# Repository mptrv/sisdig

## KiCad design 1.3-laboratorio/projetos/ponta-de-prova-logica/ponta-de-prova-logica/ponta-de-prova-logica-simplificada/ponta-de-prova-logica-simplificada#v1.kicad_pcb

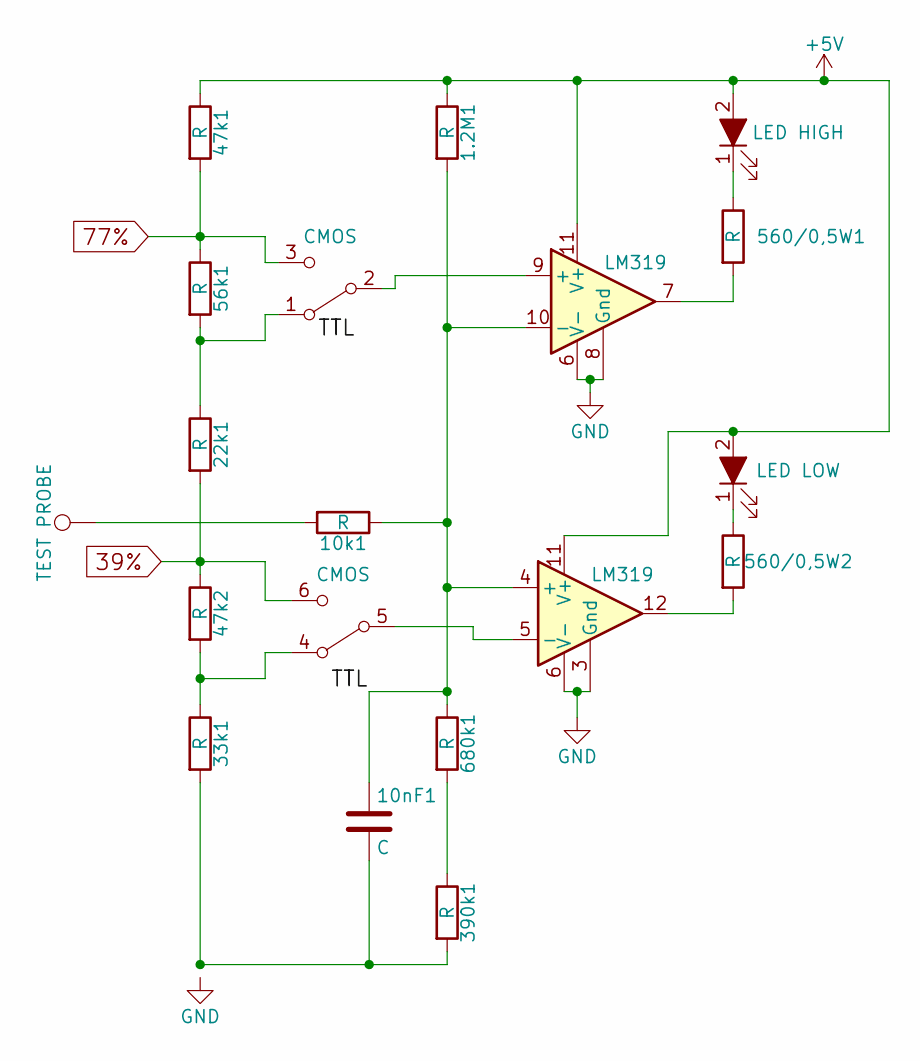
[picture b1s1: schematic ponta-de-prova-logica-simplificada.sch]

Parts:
1.2M1, 10k1, 22k1, 33k1, 47k1, 47k2, 56k1, 390k1, 560/0,5W1, 560/0,5W2, 680k1: R; R_Axial_DIN0207_L6.3mm_D2.5mm_P7.62mm_Horizontal
10nF1: C; C_Disc_D5.0mm_W2.5mm_P2.50mm
D1: LED HIGH; LED_D1.8mm_W1.8mm_H2.4mm_Horizontal_O1.27mm_Z1.6mm
D2: LED LOW; LED_D1.8mm_W1.8mm_H2.4mm_Horizontal_O1.27mm_Z1.6mm
J1: TEST PROBE; Pin_d1.0mm_L10.0mm
TTL1: CMOS; SW_CuK_JS202011AQN_DPDT_Angled
U1: LM319; DIP-14_W7.62mm

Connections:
39%: 22k1.2, 47k2.1, TTL1.6 (C)
77%: 47k1.2, 56k1.1, TTL1.3 (C)
+5V: 1.2M1.1, 47k1.1, D1.2 (A), D2.2 (A), U1.11 (V+)
GND: U1.3 (Gnd), U1.6 (V-), U1.8 (Gnd)
unnamed: 1.2M1.2, 10k1.1, 10nF1.1, 680k1.1, U1.4 (+), U1.10 (-)
unnamed: 10k1.2, J1.1
unnamed: 10nF1.2, 33k1.2, 390k1.2
unnamed: 22k1.1, 56k1.2, TTL1.1 (A)
unnamed: 33k1.1, 47k2.2, TTL1.4 (A)
unnamed: 390k1.1, 680k1.2
unnamed: 560/0,5W1.1, D1.1 (K)
unnamed: 560/0,5W1.2, U1.7
unnamed: 560/0,5W2.1, D2.1 (K)
unnamed: 560/0,5W2.2, U1.12
unnamed: TTL1.2 (B), U1.9 (+)
unnamed: TTL1.5 (B), U1.5 (-)

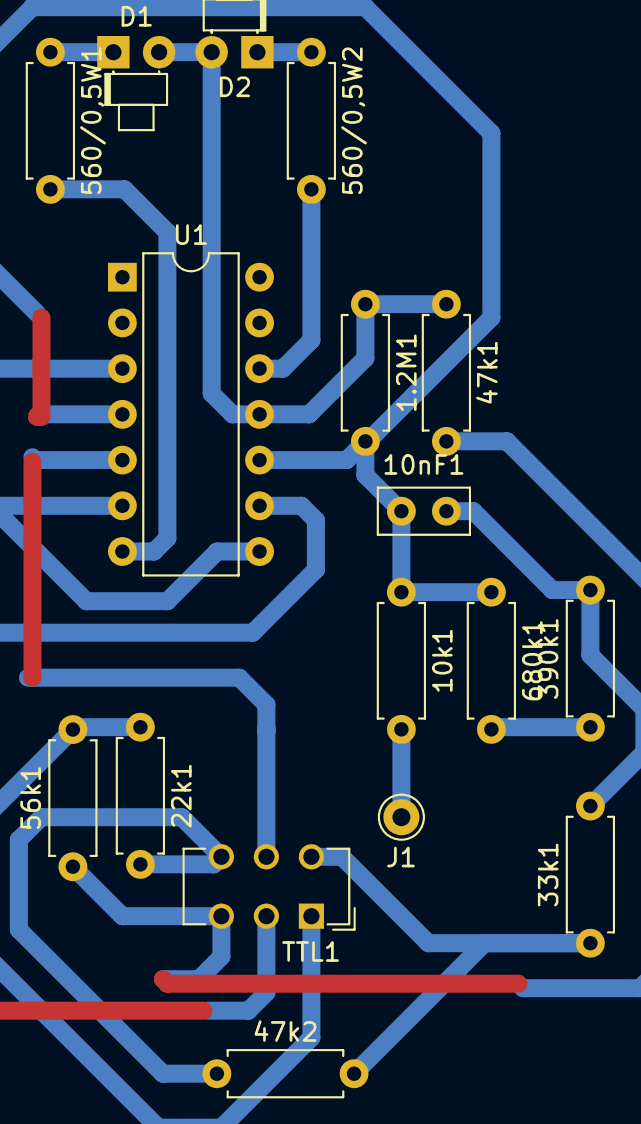
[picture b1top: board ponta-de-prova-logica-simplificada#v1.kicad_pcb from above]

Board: 2 copper layers, 17 parts (0 on the bottom side), 16 nets.
